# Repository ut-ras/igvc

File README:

IGVC2014
========

Code for the Universtiy of Texas Robotics and Automation Society's entry in IGVC 2014

Installation instructions:
cd
mkdir igvc_ros && cd igvc_ros
rosws init . /opt/ros/hydro
[Download igvc.rosinstall]
rosws merge [path to igvc.rosinstall]
rosws update

Edit your bashrc and add:
source $HOME/igvc_ros/setup.bash
export GAZEBO_MODEL_PATH=`rospack find igvc_sim`/models:$GAZEBO_MODEL_PATH
export GAZEBO_PLUGIN_PATH=`rospack find igvc_sim`/plugins:$GAZEBO_PLUGIN_PATH

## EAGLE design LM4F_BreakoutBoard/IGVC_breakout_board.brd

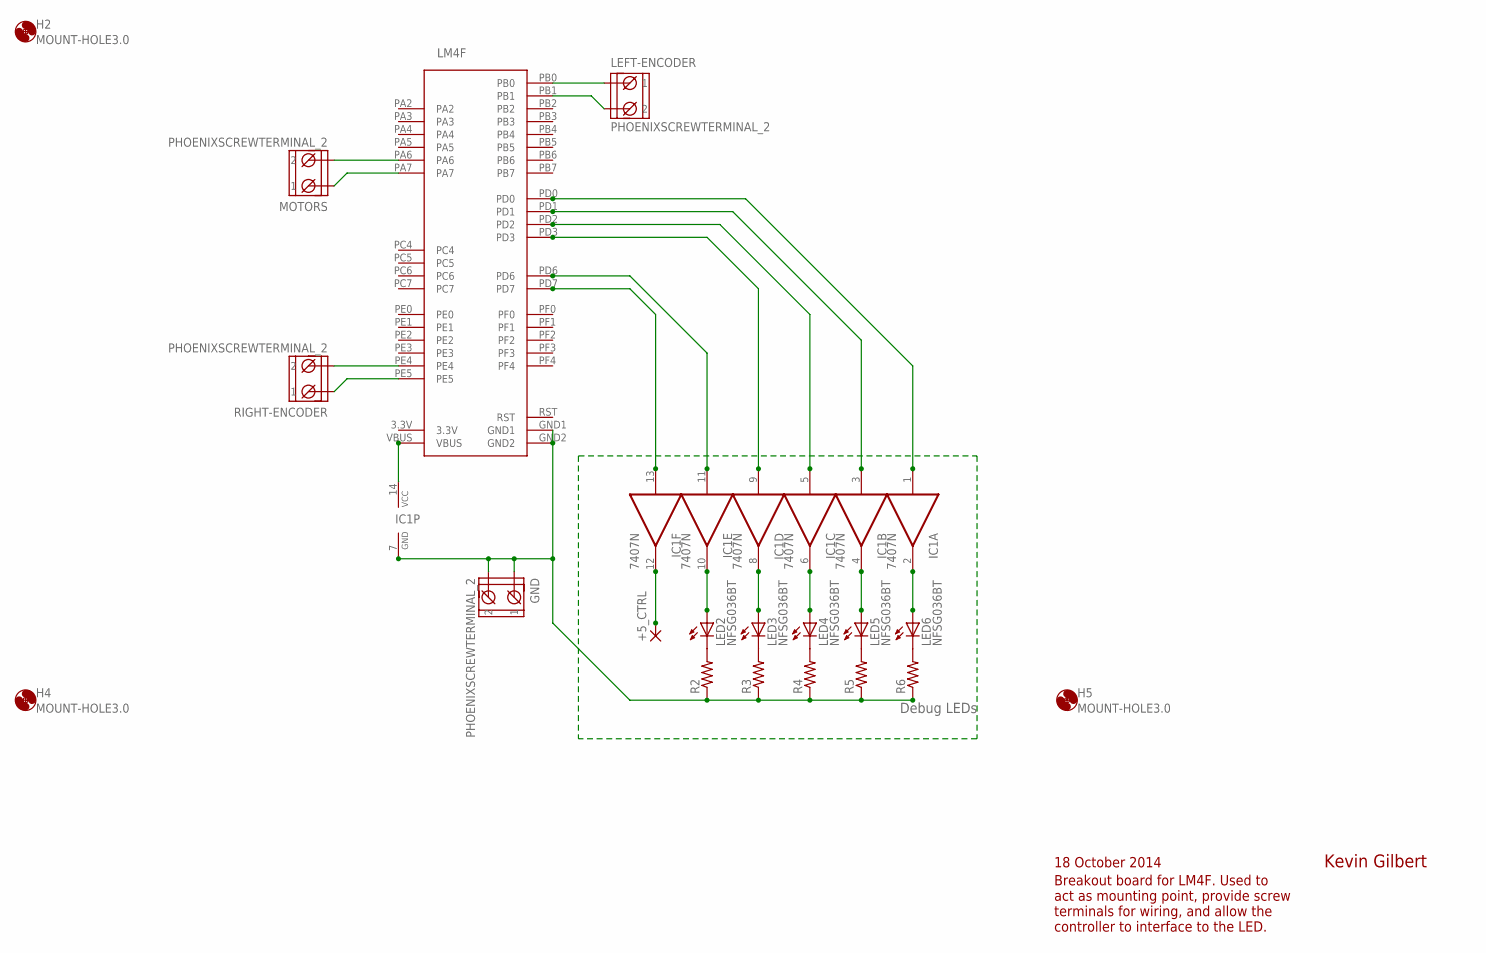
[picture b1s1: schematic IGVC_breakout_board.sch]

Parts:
+5_CTRL: 1,6/0,8
GND: PHOENIXSCREWTERMINAL_2
H2, H4, H5: MOUNT-HOLE3.0; 3,0
IC1: 7407N; DIL14
LED2, LED3, LED4, LED5, LED6: NFSG036BT
LEFT-ENCODER: PHOENIXSCREWTERMINAL_2
LM4F: STELLARIS-LAUNCHPADSTELLARIS-LAUNCHPAD-XL; LAUNCHPAD-XL
MOTORS: PHOENIXSCREWTERMINAL_2
R2, R3, R4, R5, R6: R-US_M0805; M0805
RIGHT-ENCODER: PHOENIXSCREWTERMINAL_2

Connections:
3.3V: LM4F.3.3V
GND: GND.1, GND.2, IC1.7 (GND), LM4F.GND1, LM4F.GND2, R2.1, R3.1, R4.1, R5.1, R6.1
LEFT: IC1.1 (I), LM4F.PD0
unnamed: LM4F.PE4, RIGHT-ENCODER.2
unnamed: LM4F.PA6, MOTORS.2
unnamed: LM4F.PA7, MOTORS.1
unnamed: LM4F.PE5, RIGHT-ENCODER.1
unnamed: LEFT-ENCODER.1, LM4F.PB0
unnamed: LEFT-ENCODER.2, LM4F.PB1
unnamed: +5_CTRL.1, IC1.12 (O)
unnamed: LED2.C, R2.2
unnamed: LED3.C, R3.2
unnamed: LED4.C, R4.2
unnamed: LED5.C, R5.2
unnamed: LED6.C, R6.2
unnamed: IC1.10 (O), LED2.A
unnamed: IC1.8 (O), LED3.A
unnamed: IC1.6 (O), LED4.A
unnamed: IC1.4 (O), LED5.A
unnamed: IC1.2 (O), LED6.A
unnamed: IC1.3 (I), LM4F.PD1
unnamed: IC1.5 (I), LM4F.PD2
unnamed: IC1.9 (I), LM4F.PD3
unnamed: IC1.11 (I), LM4F.PD6
unnamed: IC1.13 (I), LM4F.PD7
RST: LM4F.RST
VBUS: IC1.14 (VCC), LM4F.VBUS

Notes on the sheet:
Kevin Gilbert
18 October 2014
Breakout board for LM4F. Used to act as mounting point, provide screw terminals for wiring, and allow the controller to interface to the LED.
Debug LEDs

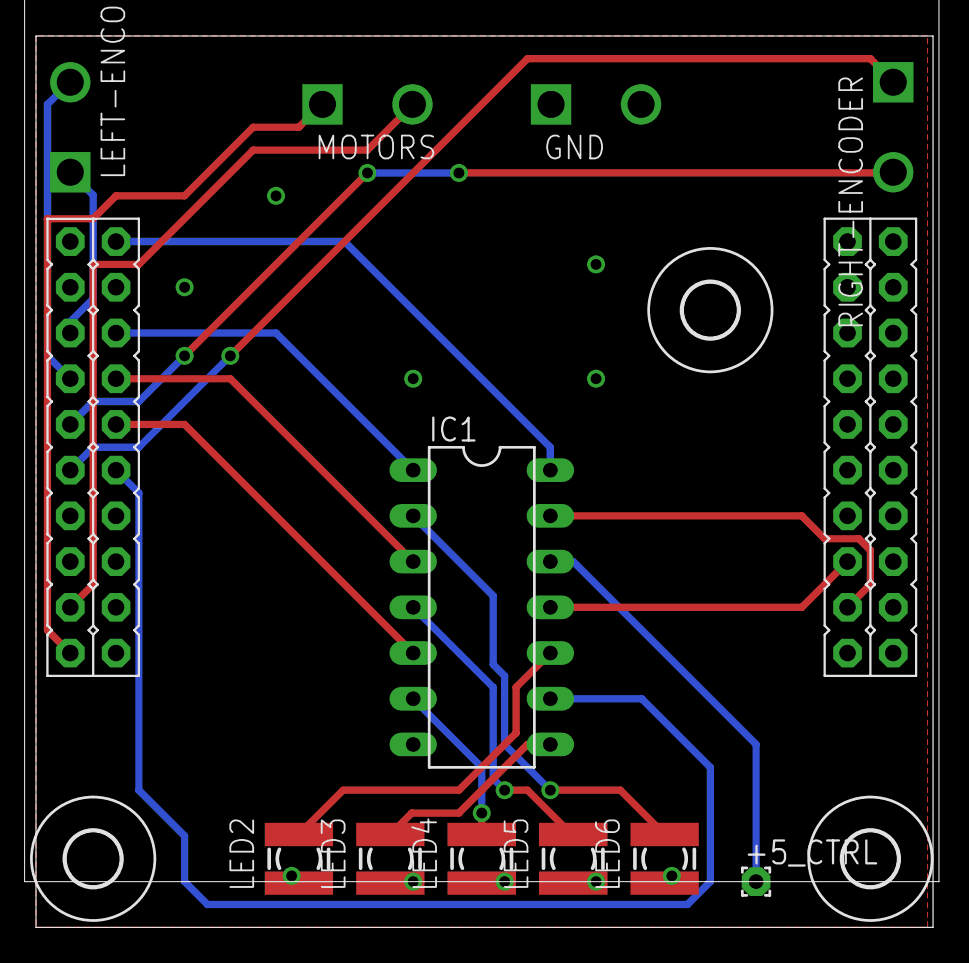
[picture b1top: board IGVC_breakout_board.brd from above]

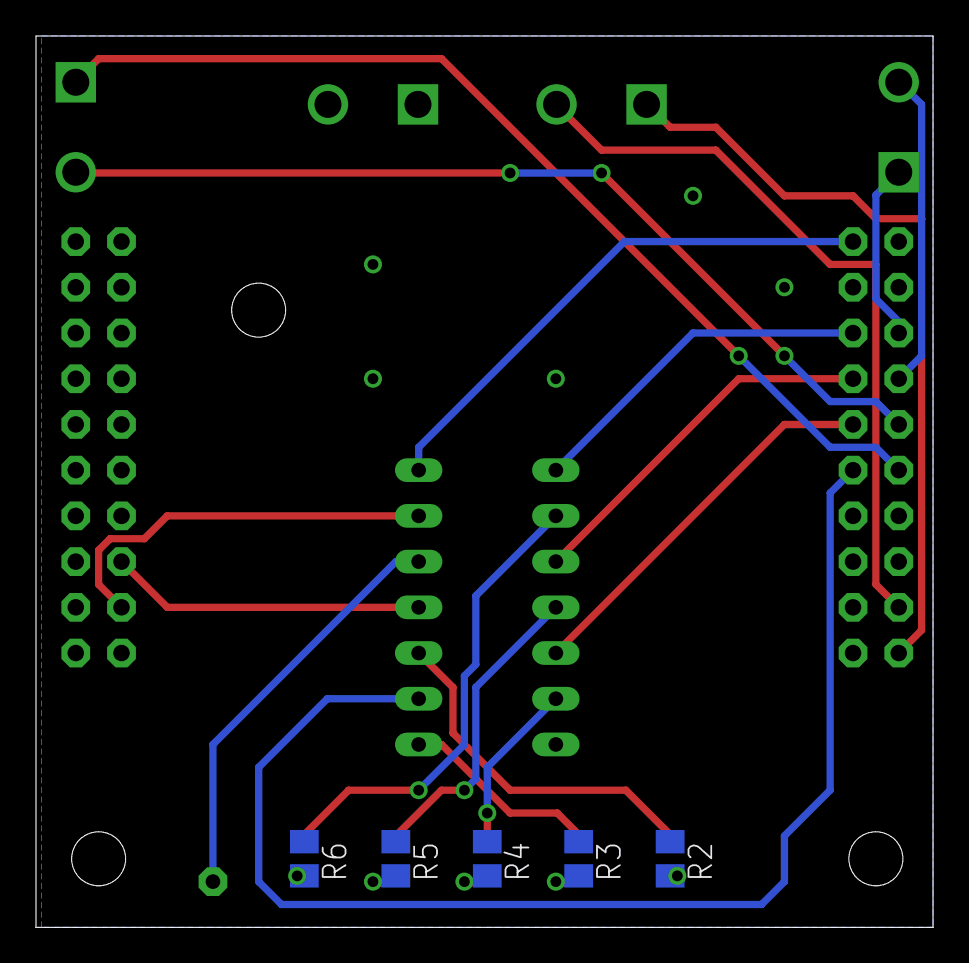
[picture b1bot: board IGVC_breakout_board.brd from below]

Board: 2 copper layers, 49.8 x 49.5 mm, 20 parts (5 on the bottom side), 25 nets.

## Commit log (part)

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2013-11-26 created workspace, ignoring build and devel directories
2013-11-26 added empty vn200 package
2013-11-26 copied vn200 driver from igvc2013 package
2013-11-26 copied over msg files from igvc2013 vn200 package, manually added them to CMakeLists.txt to compile package
2013-11-26 edited vn200 driver to use imu_vn200 package name
2013-11-26 added ras to readme
2013-11-26 added empty launchpad package
2013-11-26 added josh b.'s mechanical designs as a submodule
2013-11-30 changed maintainer name because I do not embody ras :P
2013-12-01 lm4f directory for IGVC2014 first commit. Basic json parsing set up for set motor powers and set velocity commands. Handlers do not yet contain required functions.
2013-12-01 Fixed spacing
2013-12-02 updated mechanical design submodule
2013-12-09 Integrated linux-port with JSON code to flash from Toast. Makefiles access StellarisWare/CortexM4 libraries from home directory to avoid polluting repo
2013-12-09 removed compiled files from repo
2014-01-12 added inital gps driver, I have no idea if it compiles
2014-01-18 Updated lm4f ROS Node files for initial JSON protocol approach
2014-01-19 lm4f node basic functionality with Robbys JSON LM4F module
2014-01-19 Repushed json lm4f-side code
2014-01-20 removed extra files
2014-01-21 refactored driver to be a higher-order function that accepts a callback
2014-01-21 added mock up driver for off-line testing
2014-01-22 Updated LM4F Node to run using Twist message format. TODO: dynamic conversion of Twist to JSON, update channel names to match IGVC document (/vel_cmd)
2014-01-23 made the filename more python-friendly
2014-01-26 added the node that is a gps driver
2014-01-27 working core lm4f node before merge
2014-02-01 tested, publishes when connected to gps
2014-02-01 made it a ream boy
2014-02-01 typo fixxed
2014-02-01 added submodule to fix gps_common dependency
2014-02-01 fixed scoping issue
2014-02-01 made no-fix the right value
2014-02-01 LM4F launch node reflashes LM4F on startup to reset board
2014-02-02 added pyc files to gitignore
2014-02-02 added occupancy grid package and untested maker node
2014-02-02 Added untested trinocular obstacle / lane detection.
2014-02-02 Generalized the vision algorithm to N cameras
2014-02-04 the srv files I forgot to add
2014-02-04 the relative position node now correctly gives the relative position of the waypoints when asked nicely
2014-02-05 Added check for image coordinate bounds
2014-02-05 made the launchfile work on the igvc computer
2014-02-10 Added calibration and launch file for ROS's stereo using the digital innovation cameras
2014-02-10 inital crap data node (Common Lisp!) (breaks build)
2014-02-10 made the lisp code build into an executable; will likely break builds
    testing will _need_ to be done on the IGVC computer/debian machine to verifiy correct behavior across devel and deployment platforms
    if the build breaks you can:
    * delete this directory (imu_processor) without telling git
    * install the roslisp-groovy package (contact me for archlinux PKGBUILD)
    * complain incessantly (possibly your best option)
    Have a nice day.
2014-02-11 made a filter function just in case we need to filter
    drunk coding for ~1 hour
2014-02-11 the cute cl-node now filters it's constant input (so cute! (and useless))
2014-02-11 the cl-node is growing up! it now thinks (read: converts from imu to heanding)
2014-02-11 made a launchfile for the final product (this might be it!) (needs testing)
2014-02-11 added a cl imu mock up node
2014-02-11 made the imu mock-up node build
2014-02-11 well that took a while, but it works now
    you should know that my computer is of by -6 hours (add 6 hours to commit time to get real time e.g. it is not 12:30 in the morning it is 6:30)
2014-02-11 fixed divide by zero error in mockup
2014-02-15 removed useless node
2014-02-15 added comments that point to the GSOF protocoll description
2014-02-15 made the ekf listen to the relative position from the gps
2014-02-15 lm4f ros Node sends correct Twist sections to lm4f
2014-02-15 removed diff file from lm4f_src, changed default values in json parser buffers
2014-02-15 allowed sensors to update their covarience matrix and made the gps update it's
2014-02-15 fixes issue #1
2014-02-15 fixed ekf node to subscribe to gps/trimble/pose; related to fixed issue #1
2014-02-15 added extended kalman filter package
2014-02-15 added tf broadcaster to ekf
2014-02-15 added dataReceived checks
2014-02-16 refactored ekf code to make it easier to add new sensors
2014-02-17 trimble callbacks use pose instead of odom; shortened quaternion copying code
2014-02-23 sim basically works
2014-02-23 Added control, feedback, and ameliorated some simulation stability issues
2014-02-23 Forgot to add some files
2014-02-23 Cleaned up excessive texture files
2014-02-24 Forgot to add fov specs for current cameras
2014-02-24 put check for data received out of ekf publishing loop, added some logs, added fake sensor data node for testing
2014-02-24 fixed syntax from testing with fake data
2014-03-01 added joystick driver from 2013
2014-03-01 renamed joystick driver node
2014-03-23 Calibrated new cameras
2014-03-31 Branch embedded created
2014-04-01 lm4fNode and json script running
2014-04-01 watchdog implemented
2014-04-01 removed redundent Main file
2014-04-03 Fixed a bunch of bugs in vision code. Still not working in simulation, most likely due to weird camera rotation issues (the set of points that the camera thinks it can see does not make sense based o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
2014-04-03 Line detection works in sim, obstacle detection still broken
2014-04-08 lm4f joystick node
2014-04-19 added udev rules
2014-04-25 Moved velocity control into handlers.c
2014-04-29 added round to lm4fJoystick to fix port crashing bug
2014-04-29 the makefile now uses gcc's print-search-paths method of autodetecting the library paths
2014-04-30 tweaked scaling to make turning a bit easier
2014-04-30 set pwm limits in rosnode so that it doesnt depend on ucontroller code
2014-05-14 Basic automatic ground thresholding working
2014-05-14 Added k-means clustering for color regions
2014-05-14 added ability to expand color regions
2014-05-18 Lots of progress on vision, mostly just need filtering and laser scan conversion now
2014-05-21 Added untested code for cloud assimilationand filtering
2014-05-23 fixed the driver launchfile to correctly include vn200
2014-05-23 added a get 0,0 service in the gps relativizer
2014-05-24 added launch file for ekf and the nodes it depends on
2014-05-24 added initial nav stack configuration package
2014-05-25 Updated the model to be closer to reality, added conversion to PointCloud (not 2), did some filter tuning
2014-05-25 Fixed ROS nav configuration. The sim robot can now navigate to nearby poses, avoiding obstacles along the way.
2014-05-25 gilbert made the vn200 work on Hal
2014-05-25 Added hardcoded range of known obstacle color values to reduce bad behavior in the event that we sample some line pixels
2014-05-26 fixed my math added testing to imu-to-yaw
2014-05-26 Fixed time-syncing in cloud_assimilator
2014-05-27 Added laser scan output (better than point cloud because it doesn't include obscured points)
2014-05-27 Made it so you can turn off checking for known bad obstacles more easily
2014-05-27 maybe fixed a build error in gps stufF
2014-05-27 added services as dependency for cpp
2014-05-27 assigned the cameras to usb ports in software
2014-05-27 Fixed catkin dependancies
2014-05-28 lm4f node now publishing twist
2014-05-28 tweaked maxpwm, publish rate, spacing in lm4f code
2014-05-28 added navlib as a submodule
2014-05-28 ignoring bags
2014-05-28 added some camera calibration file
2014-05-28 added lm4f bypass node, modified hardward launchfile, new mech design commits
2014-05-29 started gmaps visualizer of gps and imu data
2014-05-29 added rotation to gmaps visualization
2014-05-30 made it use atan2; now publishes between 0 and 2pi
2014-05-31 added device parameter to joystick
2014-05-31 launchfile to fire up ucontroller and joystick
2014-05-31 echoing data from computer, also sending ticks
2014-05-31 began pid tuning
2014-05-31 gave the gps a static ip and passed it in
2014-05-31 tried and failed to added a pid reset flag
2014-05-31 removed unnecessary code
2014-06-01 Changed model to hopefully final version
2014-06-01 added conversions between ang/lin vels and left/right ticks, also it drives like a dream
2014-06-01 moved ekf to launch from perception, made an imu launch file, imu-to-yaw now publishing to /imu/vn200/heading, ekf now publishing tf transform between map and base_link
2014-06-01 Added drive_path
2014-06-01 renamed lm4fJoystick node, updated joystick and navstack launch files
2014-06-01 updated ekf launch file, fixed lm4f node to publish empty messages as soon as it starts
2014-06-01 Added polygon sample regions to the vision node
2014-06-01 made gps added to ekf optional, added debugging statements to ekf, fixed angle wrapping error
2014-06-01 Made local planner not care about orientation
2014-06-01 Fixed possible bug in cloud_assimilator
2014-06-02 fixed ekf time bug
2014-06-02 removed I term in PID, josh tweaked camera orientation, removed gps/ins msgs from vn200, lowered yaw goal tolerance, increase angle_inc param to cloud_assimilator, tweaked init polygon samples, remap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
2014-06-02 made a launch file to test barrel bag
2014-06-02 added the model
2014-06-02 redid color sample polygons
2014-06-05 aded imu_tools submodule
2014-06-05 removed occupancy_grid package, added odom topic to the move_base launch, fixed typo in ekf
2014-06-05 refactored the xor checksum loops
2014-06-05 fixed indentation bug that rate-limited the driver to 6.6hz
2014-06-05 removed unneeded global
2014-06-05 converted the read_data function to use readline
2014-06-05 refactored init process to use a 'const' structure of commands to send
2014-06-05 refactored main loop
2014-06-06 increased sample rate to 200 (imu limited)
2014-06-06 fixes issue #19
2014-06-06 added rasware checked out to igvc branch as a submodule
2014-06-06 removed old lm4f stuff
2014-06-06 much refactoring was had and there was rejoicing throughout the land
2014-06-06 lm4f driver now listens to /cmd_vel
2014-06-06 maybe added an imu filter.
2014-06-07 Revert "maybe added an imu filter."
    This reverts commit 932f4d7c2b99becd063d397259e3fa67d4f74bff.
2014-06-07 added custom lm4f debug msg
2014-06-07 now publishing on custom debug msg
2014-06-07 put back the code loading lm4f code on startup
2014-06-07 removed unused files from lm4f code
2014-06-07 stupid cherrypick changing hashes ugh
2014-06-07 stupid cherrypick screwing up hashes
2014-06-07 removing embedded/lm4f and navlib submodules
2014-09-15 Added a doc directory for loose documentation. Currently has design report from 2014.
2014-09-25 Removed scripts directory in ucontroller catkin workspace. LM4F nodes in /ucontroller/src
2014-10-05 De-catkinized and reorganized the codebase. Possibly broke all the things.
2014-10-05 Added rosinstall and instructions, removed git external repos
2014-10-05 Hopefully fixed readme text
2014-10-05 Fixed README
2014-10-09 Added RASware IGVC branch as a submodule for embedded code in new stack and updated path info in lm4f ROS node. LM4F_Driver runs now.
2014-10-18 Start of schematic/board files for a LM4F Breakout board for IGVC. Allows for easier mounting to the frame, screw terminals for wire management, and a controlelr circuit for the autonomous mode LED.
2014-10-18 Cleaned up extra files.
2014-10-18 Ground plane added and traces routed. First design iteration pretty much completed and ready to test.
2014-10-18 Basic silk screen added to label outputs
2014-10-18 Added labels for individual motor outputs
2014-10-19 Added BOM from bom.ulp
2014-11-24 added basic lm4f driver shell for debugging on console
2015-02-08 swapped terminals from rachel's RAS eagle lib
2015-02-08 re-boarded to fit within 5cm x 5cm
2015-02-16 changed the dev of imu-driver to be by-id
